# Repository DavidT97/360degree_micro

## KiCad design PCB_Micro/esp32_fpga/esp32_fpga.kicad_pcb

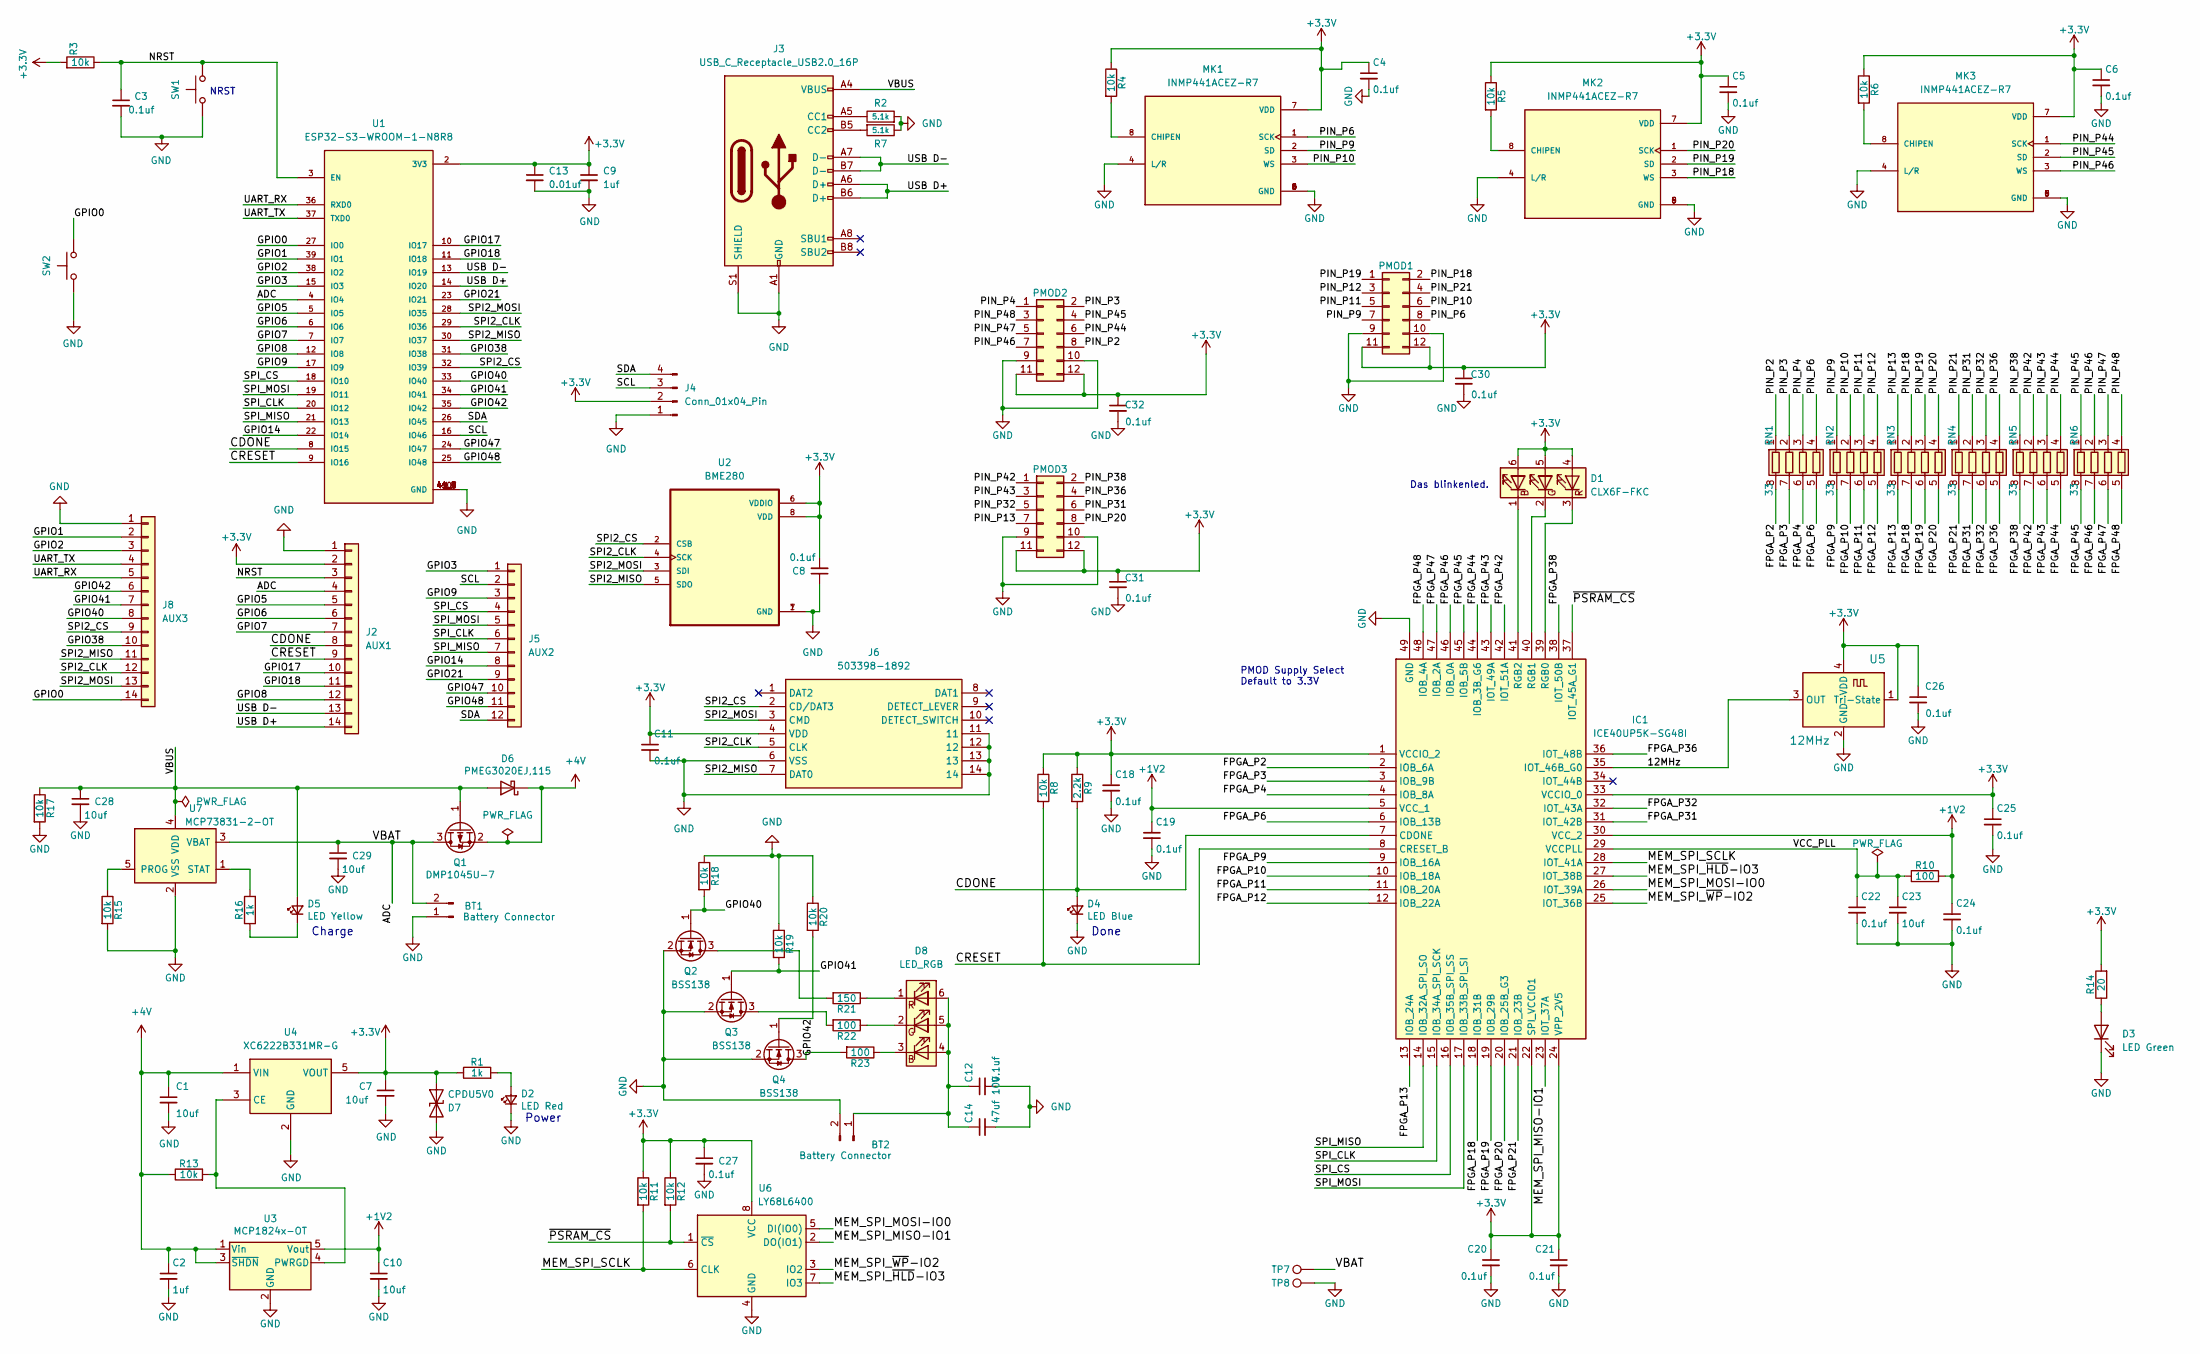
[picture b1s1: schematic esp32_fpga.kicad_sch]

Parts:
BT1: Battery Connector; JST_EH_S2B-EH_1x02_P2.50mm_Horizontal
BT2: Battery Connector; JST_EH_B2B-EH-A_1x02_P2.50mm_Vertical
C1, C7, C10, C23, C28, C29: 10uf; C_0805_2012Metric
C2, C9: 1uf; C_0603_1608Metric
C3, C4, C5, C6, C8, C11, C12, C18, C19, C20, C21, C22, C24, C25, C26, C27, C30, C31, C32: 0.1uf; C_0402_1005Metric
C13: 0.01uf; C_0603_1608Metric
C14: 47uf 10V; C_0402_1005Metric
D1: CLX6F-FKC; LED_RGB_PLCC-6
D2: LED Red; LED_0603_1608Metric
D3: LED Green; LED_0201_0603Metric
D4: LED Blue; LED_0603_1608Metric
D5: LED Yellow; LED_0603_1608Metric
D6: PMEG3020EJ,115; D_SOD-323F
D7: CPDU5V0; D_0603_1608Metric
D8: LED_RGB; LED_RGB_5050-6
IC1: ICE40UP5K-SG48I; QFN50P700X700X100-49N-D; Mouser Part Number 842-ICE40UP5K-SG48I
J2: AUX1; PinSocket_1x14_P1.00mm_Vertical
J3: USB_C_Receptacle_USB2.0_16P; USB_C_Receptacle_GCT_USB4105-xx-A_16P_TopMnt_Horizontal
J4: Conn_01x04_Pin; PinSocket_1x04_P2.54mm_Vertical
J5: AUX2; PinSocket_1x12_P1.00mm_Vertical
J6: 503398-1892; 5033981892; Mouser Part Number 538-503398-1892
J8: AUX3; PinSocket_1x14_P1.00mm_Vertical
MK1, MK2, MK3: INMP441ACEZ-R7; MIC_INMP441ACEZ-R7; PARTREV 1.1
PMOD1, PMOD2, PMOD3: CONN_02X06; Samtec_HLE-106-02-xx-DV-TE_2x06_P2.54mm_Horizontal
Q1: DMP1045U-7; SOT-23
Q2, Q3, Q4: BSS138; SOT-23
R1, R16: 1k; R_0603_1608Metric
R2, R7: 5.1k; R_0402_1005Metric; LCSC C25905
R3, R4, R5, R6, R8, R11, R12, R13, R15, R17, R18, R19, R20: 10k; R_0603_1608Metric
R9: 2.2k; R_0603_1608Metric
R10, R22, R23: 100; R_0603_1608Metric
R14: 20; R_0603_1608Metric
R21: 150; R_0603_1608Metric
RN1, RN2, RN3, RN4, RN5, RN6: 33; R_Array_Concave_4x0402
SW1, SW2: SW_Push; SW_SPST_PTS810
TP7: VBATT; TestPoint_Pad_D1.0mm
TP8: GND; TestPoint_Pad_D1.0mm
U1: ESP32-S3-WROOM-1-N8R8; XCVR_ESP32S3WROOM1N8R8
U2: BME280; PSON65P250X250X100-8N
U3: MCP1824x-OT; SOT-23-5
U4: XC6222B331MR-G; SOT-23-5
U5: 12MHz; Oscillator_SMD_ECS_2520MV-xxx-xx-4Pin_2.5x2.0mm
U6: LY68L6400; SOIC-8_3.9x4.9mm_P1.27mm
U7: MCP73831-2-OT; SOT-23-5

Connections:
+1V2: C10.1, C19.1, C24.1, IC1.5 (VCC_1), IC1.30 (VCC_2), R10.2, U3.5 (Vout)
+3.3V: C4.1, C5.1, C6.1, C7.1, C8.2, C9.1, C11.1, C13.1, C18.1, C20.1, C21.1, C25.1, C26.1, C27.1, C30.1, C31.1, C32.1, D1.4 (BA), D1.5 (GA), D1.6 (RA), D7.1 (A1), IC1.1 (VCCIO_2), IC1.22 (SPI_VCCIO1), IC1.24 (VPP_2V5), IC1.33 (VCCIO_0), J2.2, J4.2, J6.4 (VDD), MK1.7 (VDD), MK2.7 (VDD), MK3.7 (VDD), PMOD1.11, PMOD1.12, PMOD2.11, PMOD2.12, PMOD3.11, PMOD3.12, R1.1, R3.2, R4.1, R5.1, R6.1, R8.1, R9.1, R11.1, R12.1, R14.2, U1.2 (3V3), U2.6 (VDDIO), U2.8 (VDD), U4.5 (VOUT), U5.1 (Tri-State), U5.4 (VDD), U6.8 (VCC)
+4V: C1.1, C2.1, D6.1 (K), Q1.2 (S), R13.1, U3.1 (Vin), U3.3 (~SHDN), U4.1 (VIN)
/12MHz: IC1.35 (IOT_46B_G0), U5.3 (OUT)
/ADC: BT1.2, C29.1, J2.4, Q1.3 (D), TP7.1, U1.4 (IO4), U7.3 (VBAT)
/CDONE: D4.2 (A), IC1.7 (CDONE), J2.8, R9.2, U1.8 (IO15)
/CRESET: IC1.8 (CRESET_B), J2.9, R8.2, U1.9 (IO16)
/FPGA_P2: IC1.2 (IOB_6A), RN1.8 (R1.2)
/FPGA_P3: IC1.3 (IOB_9B), RN1.7 (R2.2)
/FPGA_P4: IC1.4 (IOB_8A), RN1.6 (R3.2)
/FPGA_P6: IC1.6 (IOB_13B), RN1.5 (R4.2)
/FPGA_P9: IC1.9 (IOB_16A), RN2.8 (R1.2)
/FPGA_P10: IC1.10 (IOB_18A), RN2.7 (R2.2)
/FPGA_P11: IC1.11 (IOB_20A), RN2.6 (R3.2)
/FPGA_P12: IC1.12 (IOB_22A), RN2.5 (R4.2)
/FPGA_P13: IC1.13 (IOB_24A), RN3.8 (R1.2)
/FPGA_P18: IC1.18 (IOB_31B), RN3.7 (R2.2)
/FPGA_P19: IC1.19 (IOB_29B), RN3.6 (R3.2)
/FPGA_P20: IC1.20 (IOB_25B_G3), RN3.5 (R4.2)
/FPGA_P21: IC1.21 (IOB_23B), RN4.8 (R1.2)
/FPGA_P31: IC1.31 (IOT_42B), RN4.7 (R2.2)
/FPGA_P32: IC1.32 (IOT_43A), RN4.6 (R3.2)
/FPGA_P36: IC1.36 (IOT_48B), RN4.5 (R4.2)
/FPGA_P38: IC1.38 (IOT_50B), RN5.8 (R1.2)
/FPGA_P42: IC1.42 (IOT_51A), RN5.7 (R2.2)
/FPGA_P43: IC1.43 (IOT_49A), RN5.6 (R3.2)
/FPGA_P44: IC1.44 (IOB_3B_G6), RN5.5 (R4.2)
/FPGA_P45: IC1.45 (IOB_5B), RN6.8 (R1.2)
/FPGA_P46: IC1.46 (IOB_0A), RN6.7 (R2.2)
/FPGA_P47: IC1.47 (IOB_2A), RN6.6 (R3.2)
/FPGA_P48: IC1.48 (IOB_4A), RN6.5 (R4.2)
/GPIO0: J8.14, SW2.1, U1.27 (IO0)
/GPIO1: J8.2, U1.39 (IO1)
/GPIO2: J8.3, U1.38 (IO2)
/GPIO3: J5.1, U1.15 (IO3)
/GPIO5: J2.5, U1.5 (IO5)
/GPIO6: J2.6, U1.6 (IO6)
/GPIO7: J2.7, U1.7 (IO7)
/GPIO8: J2.12, U1.12 (IO8)
/GPIO9: J5.3, U1.17 (IO9)
/GPIO14: J5.8, U1.22 (IO14)
/GPIO17: J2.10, U1.10 (IO17)
/GPIO18: J2.11, U1.11 (IO18)
/GPIO21: J5.9, U1.23 (IO21)
/GPIO38: J8.10, U1.31 (IO38)
/GPIO40: J8.8, Q2.1 (G), R18.2, U1.33 (IO40)
/GPIO41: J8.7, Q3.1 (G), R19.2, U1.34 (IO41)
/GPIO42: J8.6, Q4.1 (G), R20.2, U1.35 (IO42)
/GPIO47: J5.10, U1.24 (IO47)
/GPIO48: J5.11, U1.25 (IO48)
/MEM_SPI_MISO-IO1: IC1.23 (IOT_37A), U6.2 (DO(IO1))
/MEM_SPI_MOSI-IO0: IC1.26 (IOT_39A), U6.5 (DI(IO0))
/MEM_SPI_SCLK: IC1.28 (IOT_41A), R11.2, U6.6 (CLK)
/MEM_SPI_~HLD-IO3: IC1.27 (IOT_38B), U6.7 (IO3)
/MEM_SPI_~WP-IO2: IC1.25 (IOT_36B), U6.3 (IO2)
/NRST: C3.1, J2.3, R3.1, SW1.1, U1.3 (EN)
/PIN_P2: PMOD2.8, RN1.1 (R1.1)
/PIN_P3: PMOD2.2, RN1.2 (R2.1)
/PIN_P4: PMOD2.1, RN1.3 (R3.1)
/PIN_P6: MK1.1 (SCK), PMOD1.8, RN1.4 (R4.1)
/PIN_P9: MK1.2 (SD), PMOD1.7, RN2.1 (R1.1)
/PIN_P10: MK1.3 (WS), PMOD1.6, RN2.2 (R2.1)
/PIN_P11: PMOD1.5, RN2.3 (R3.1)
/PIN_P12: PMOD1.3, RN2.4 (R4.1)
/PIN_P13: PMOD3.7, RN3.1 (R1.1)
/PIN_P18: MK2.3 (WS), PMOD1.2, RN3.2 (R2.1)
/PIN_P19: MK2.2 (SD), PMOD1.1, RN3.3 (R3.1)
/PIN_P20: MK2.1 (SCK), PMOD3.8, RN3.4 (R4.1)
/PIN_P21: PMOD1.4, RN4.1 (R1.1)
/PIN_P31: PMOD3.6, RN4.2 (R2.1)
/PIN_P32: PMOD3.5, RN4.3 (R3.1)
/PIN_P36: PMOD3.4, RN4.4 (R4.1)
/PIN_P38: PMOD3.2, RN5.1 (R1.1)
/PIN_P42: PMOD3.1, RN5.2 (R2.1)
/PIN_P43: PMOD3.3, RN5.3 (R3.1)
/PIN_P44: MK3.1 (SCK), PMOD2.6, RN5.4 (R4.1)
/PIN_P45: MK3.2 (SD), PMOD2.4, RN6.1 (R1.1)
/PIN_P46: MK3.3 (WS), PMOD2.7, RN6.2 (R2.1)
/PIN_P47: PMOD2.5, RN6.3 (R3.1)
/PIN_P48: PMOD2.3, RN6.4 (R4.1)
/SCL: J4.3, J5.2, U1.16 (IO46)
/SDA: J4.4, J5.12, U1.26 (IO45)
/SPI2_CLK: J6.5 (CLK), J8.12, U1.29 (IO36), U2.4 (SCK)
/SPI2_CS: J6.2 (CD/DAT3), J8.9, U1.32 (IO39), U2.2 (CSB)
/SPI2_MISO: J6.7 (DAT0), J8.11, U1.30 (IO37), U2.5 (SDO)
/SPI2_MOSI: J6.3 (CMD), J8.13, U1.28 (IO35), U2.3 (SDI)
/SPI_CLK: IC1.15 (IOB_34A_SPI_SCK), J5.6, U1.20 (IO12)
/SPI_CS: IC1.16 (IOB_35B_SPI_SS), J5.4, U1.18 (IO10)
/SPI_MISO: IC1.14 (IOB_32A_SPI_SO), J5.7, U1.21 (IO13)
/SPI_MOSI: IC1.17 (IOB_33B_SPI_SI), J5.5, U1.19 (IO11)
/UART_RX: J8.5, U1.36 (RXD0)
/UART_TX: J8.4, U1.37 (TXD0)
/USB D+: J2.14, J3.A6 (D+), J3.B6 (D+), U1.14 (IO20)
/USB D-: J2.13, J3.A7 (D-), J3.B7 (D-), U1.13 (IO19)
/VBUS: C28.1, D5.2 (A), D6.2 (A), J3.A4 (VBUS), J3.A9 (VBUS), J3.B4 (VBUS), J3.B9 (VBUS), Q1.1 (G), R17.1, U7.4 (VDD)
/VCC_PLL: C22.1, C23.1, IC1.29 (VCCPLL), R10.1
/~PSRAM_CS: IC1.37 (IOT_45A_G1), R12.2, U6.1 (~CS)
GND: BT1.1, BT2.2, C1.2, C2.2, C3.2, C4.2, C5.2, C6.2, C7.2, C8.1, C9.2, C10.2, C11.2, C12.2, C13.2, C14.2, C18.2, C19.2, C20.2, C21.2, C22.2, C23.2, C24.2, C25.2, C26.2, C27.2, C28.2, C29.2, C30.2, C31.2, C32.2, D2.1 (K), D3.1 (K), D4.1 (K), D7.2 (A2), IC1.49 (GND), J2.1, J3.A1 (GND), J3.A12 (GND), J3.B1 (GND), J3.B12 (GND), J3.S1 (SHIELD), J4.1, J6.6 (VSS), J6.11, J6.12, J6.13, J6.14, J8.1, MK1.4 (L/R), MK1.5 (GND), MK1.6 (GND), MK1.9 (GND), MK2.4 (L/R), MK2.5 (GND), MK2.6 (GND), MK2.9 (GND), MK3.4 (L/R), MK3.5 (GND), MK3.6 (GND), MK3.9 (GND), PMOD1.9, PMOD1.10, PMOD2.9, PMOD2.10, PMOD3.9, PMOD3.10, Q2.2 (S), Q3.2 (S), Q4.2 (S), R2.2, R7.1, R15.2, R17.2, R18.1, R19.1, R20.1, SW1.2, SW2.2, TP8.1, U1.1 (GND), U1.40 (GND), U1.41_1 (GND), U1.41_2 (GND), U1.41_3 (GND), U1.41_4 (GND), U1.41_5 (GND), U1.41_6 (GND), U1.41_7 (GND), U1.41_8 (GND), U1.41_9 (GND), U1.41_10, U1.41_11, U1.41_12, U1.41_13, U1.41_14, U1.41_15, U1.41_16, U1.41_17, U1.41_18, U1.41_19, U1.41_20, U1.41_21, U2.1 (GND), U2.7 (GND), U3.2 (GND), U4.2 (GND), U5.2 (GND), U6.4 (GND), U7.2 (VSS)
unnamed: BT2.1, C12.1, C14.1, D8.4 (BA), D8.5 (GA), D8.6 (RA)
unnamed: D1.3 (BK), IC1.39 (RGB0)
unnamed: D1.2 (GK), IC1.40 (RGB1)
unnamed: D1.1 (RK), IC1.41 (RGB2)
unnamed: D2.2 (A), R1.2
unnamed: D3.2 (A), R14.1
unnamed: D5.1 (K), R16.1
unnamed: D8.3 (BK), R23.1
unnamed: D8.2 (GK), R22.1
unnamed: D8.1 (RK), R21.1
unnamed: J3.A5 (CC1), R2.1
unnamed: J3.B5 (CC2), R7.2
unnamed: MK1.8 (CHIPEN), R4.2
unnamed: MK2.8 (CHIPEN), R5.2
unnamed: MK3.8 (CHIPEN), R6.2
unnamed: Q2.3 (D), R21.2
unnamed: Q3.3 (D), R22.2
unnamed: Q4.3 (D), R23.2
unnamed: R13.2, U3.4 (PWRGD), U4.3 (CE)
unnamed: R15.1, U7.5 (PROG)
unnamed: R16.2, U7.1 (STAT)

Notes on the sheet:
Done
NRST
Power
Charge
Das blinkenled.
PMOD Supply Select Default to 3.3V

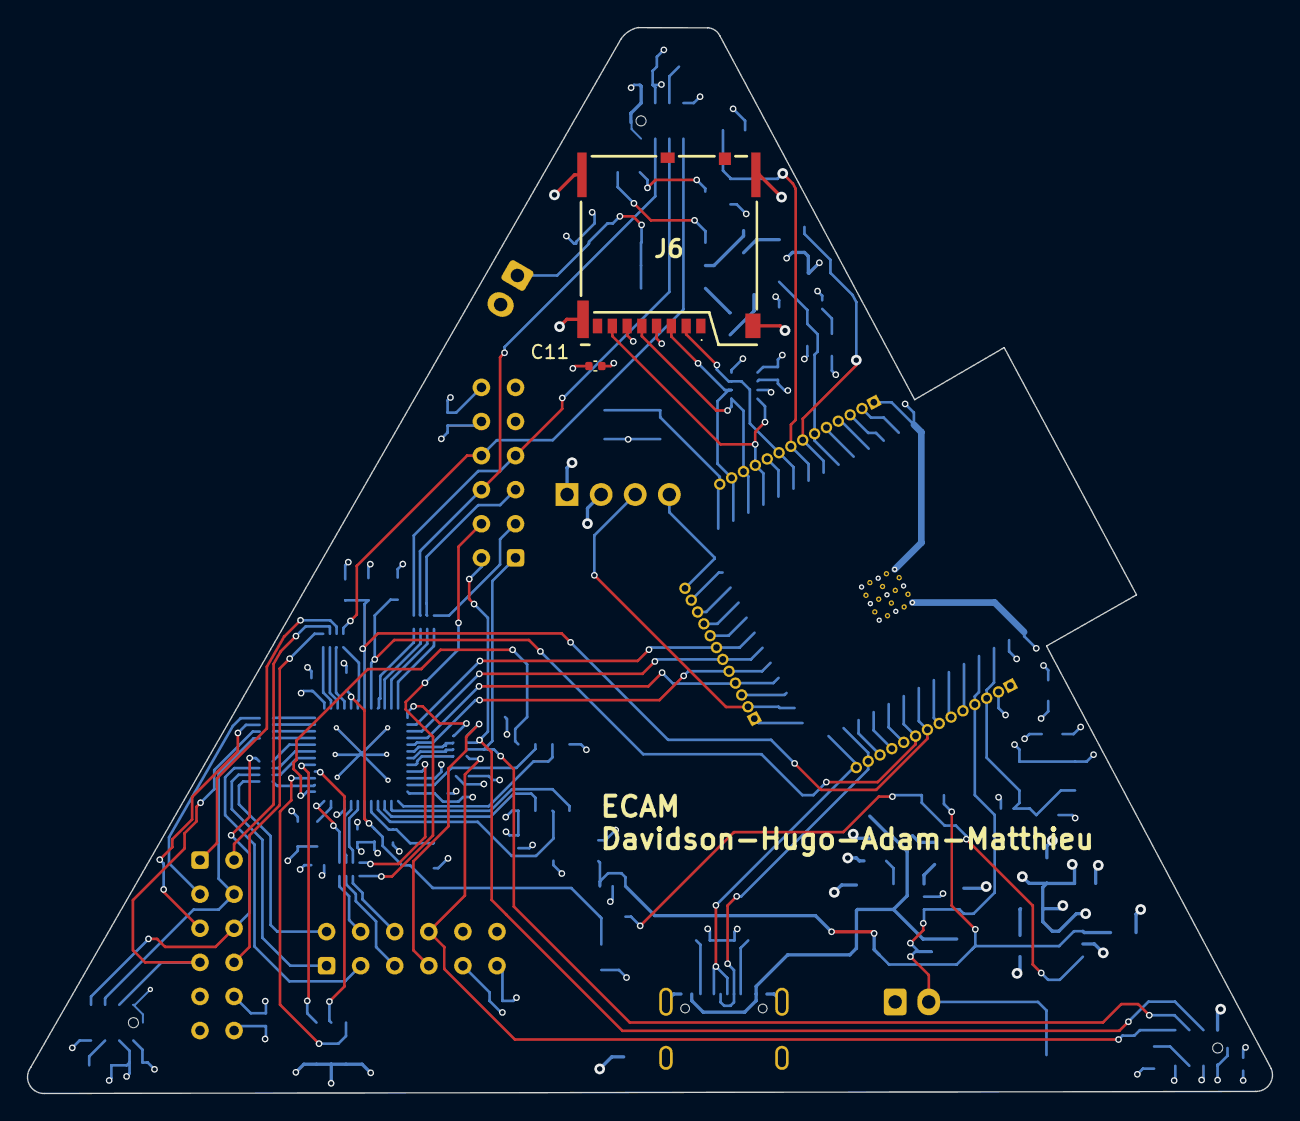
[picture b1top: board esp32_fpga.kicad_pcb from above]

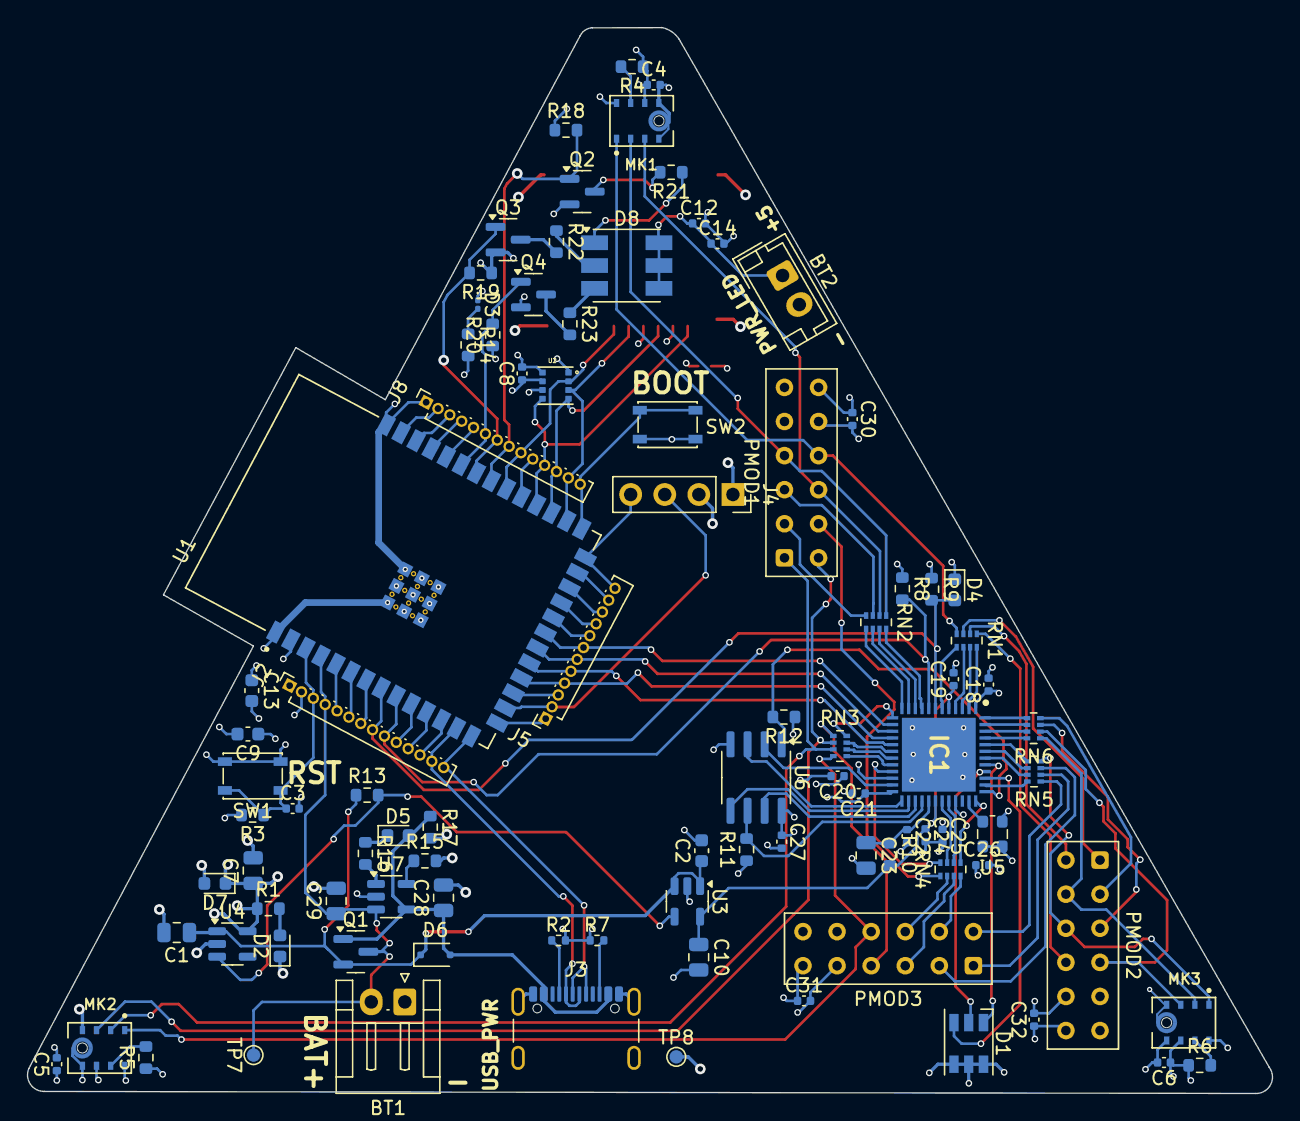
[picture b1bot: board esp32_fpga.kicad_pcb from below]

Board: 4 copper layers, 92.8 x 79.4 mm, 96 parts (94 on the bottom side), 119 nets.

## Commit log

2025-09-29 1er commit
2025-10-19 Projet KiCAD avec la schématique à contrôler
2025-10-24 schématique complet
2025-10-24 Début PCB
2025-10-24 pcb ok
2025-10-24 PCB save agencement esp32
2025-10-25 PCB presque terminé
2025-10-26 PCB rooté reste les erreurs a voir
2025-10-26 PCB terminé avec gerber sans LEDs niveau sonore
2025-10-26 Ajout de labels et modifications d'empreinte tjr sans LED
2025-10-26 PCB et schématique modifié pour l'implémentation de la LED RGB avec alim externe
